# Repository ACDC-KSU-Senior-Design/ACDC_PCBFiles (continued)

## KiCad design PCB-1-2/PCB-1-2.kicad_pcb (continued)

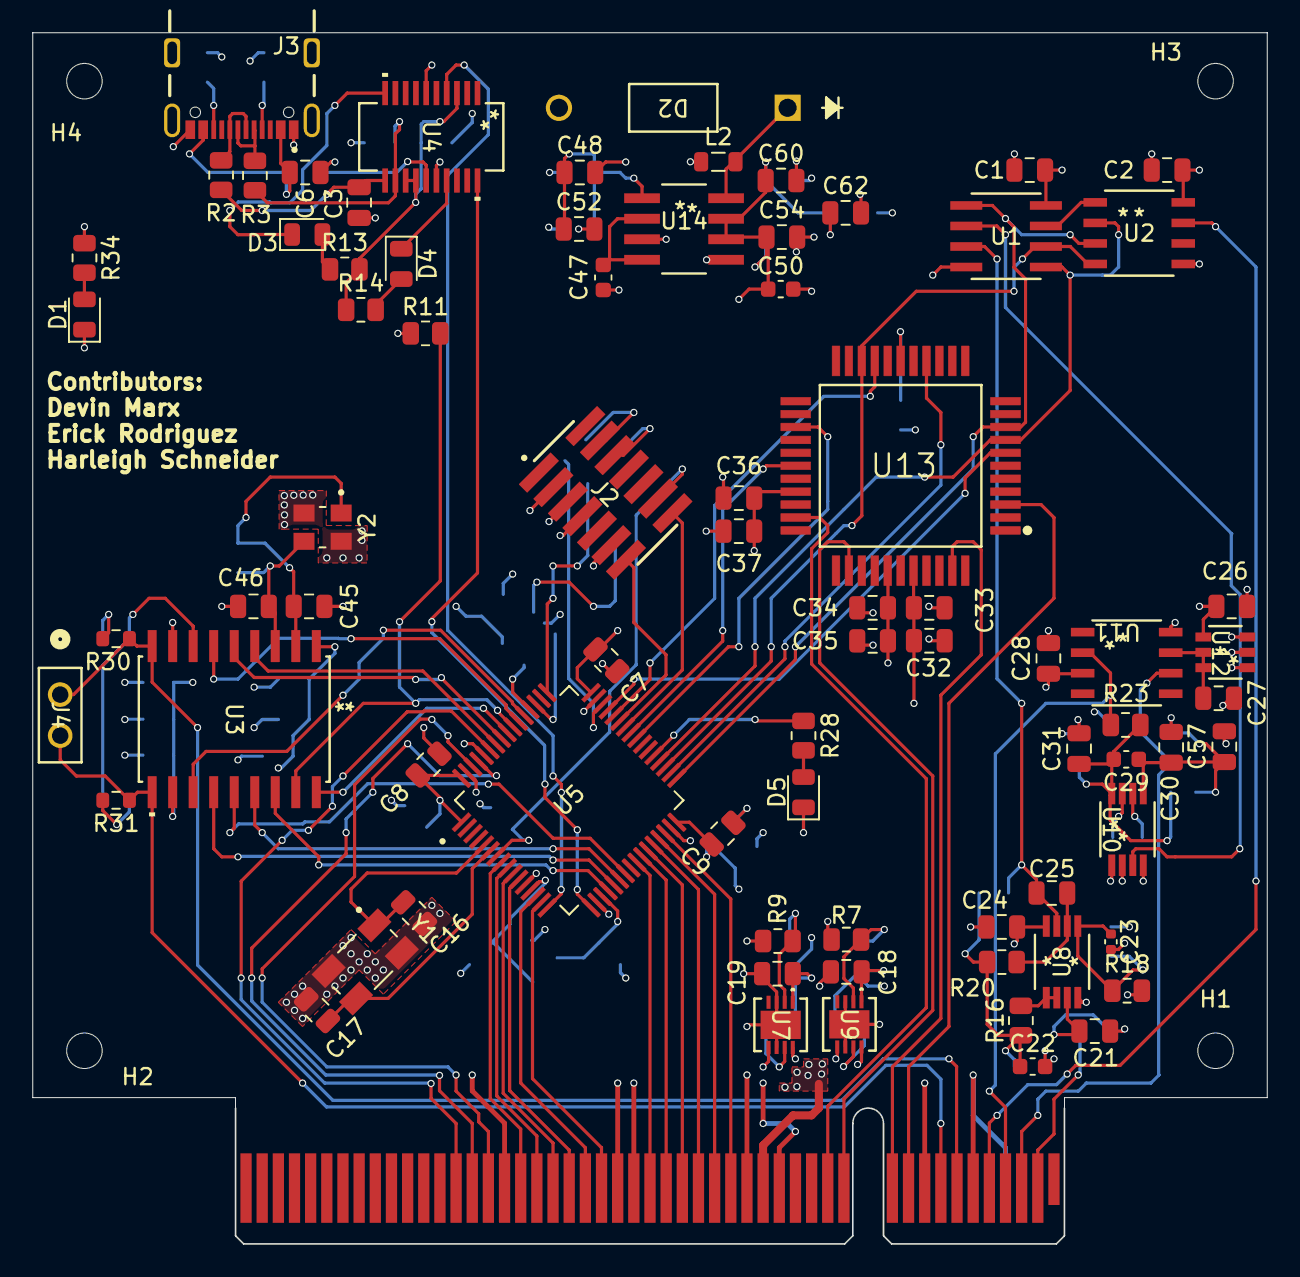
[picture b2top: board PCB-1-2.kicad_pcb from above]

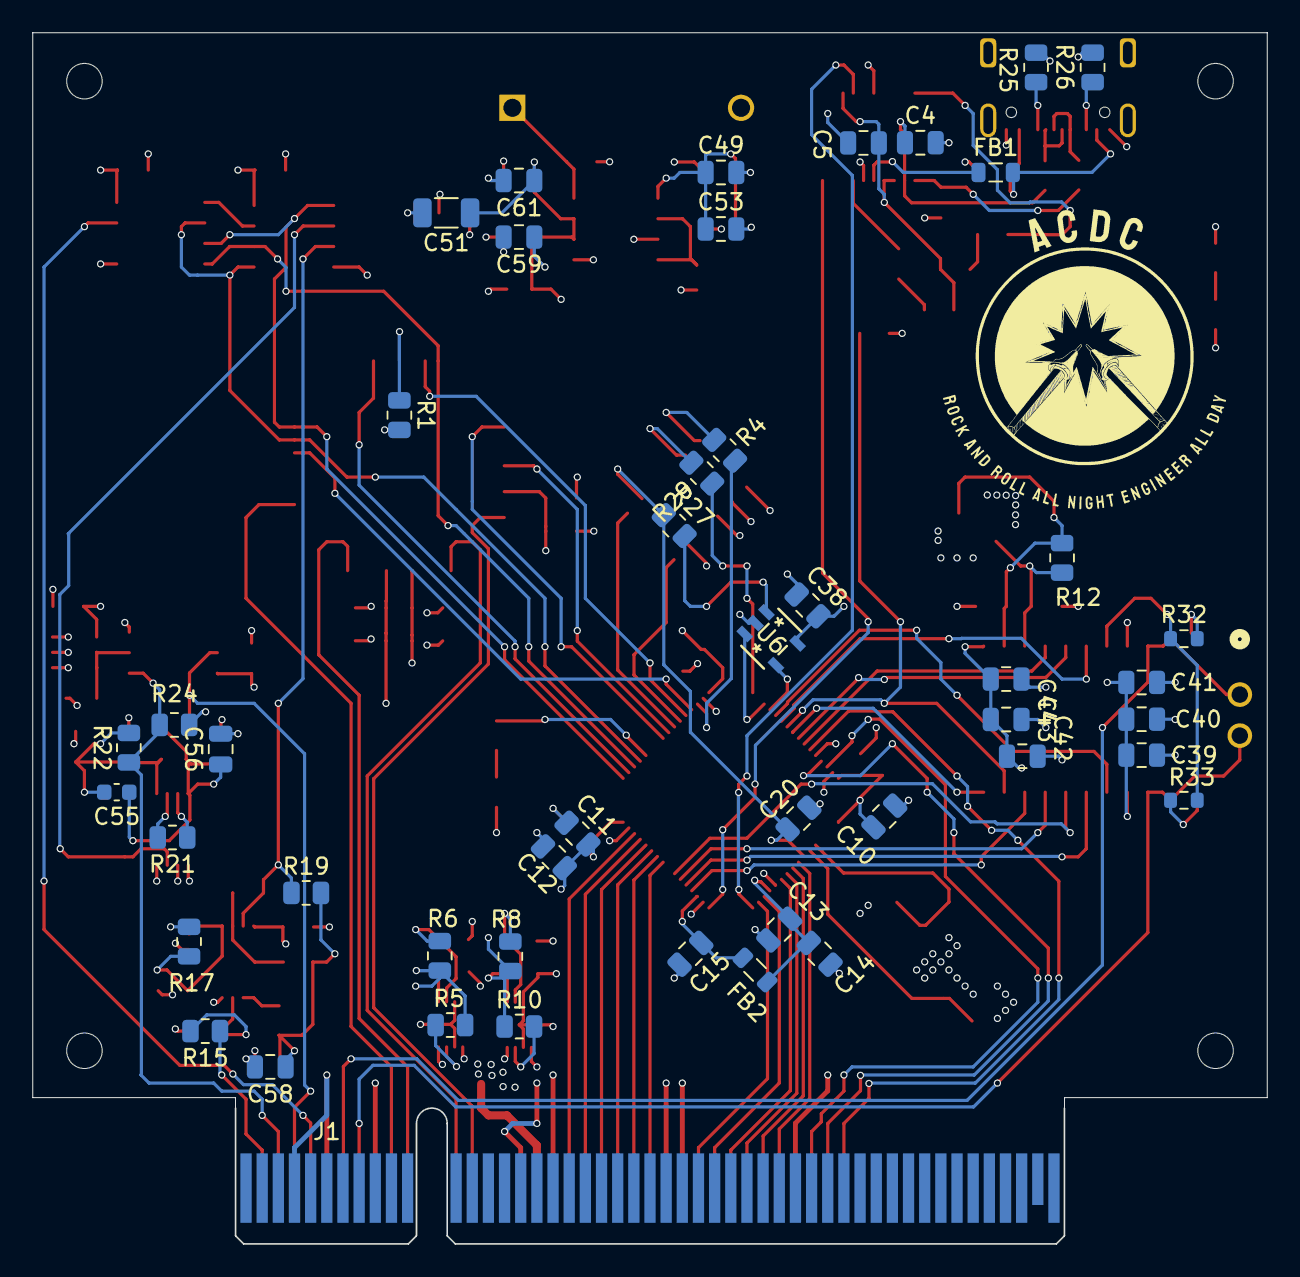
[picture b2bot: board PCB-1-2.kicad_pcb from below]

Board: 4 copper layers, 76.4 x 74.9 mm, 128 parts (47 on the bottom side), 105 nets.

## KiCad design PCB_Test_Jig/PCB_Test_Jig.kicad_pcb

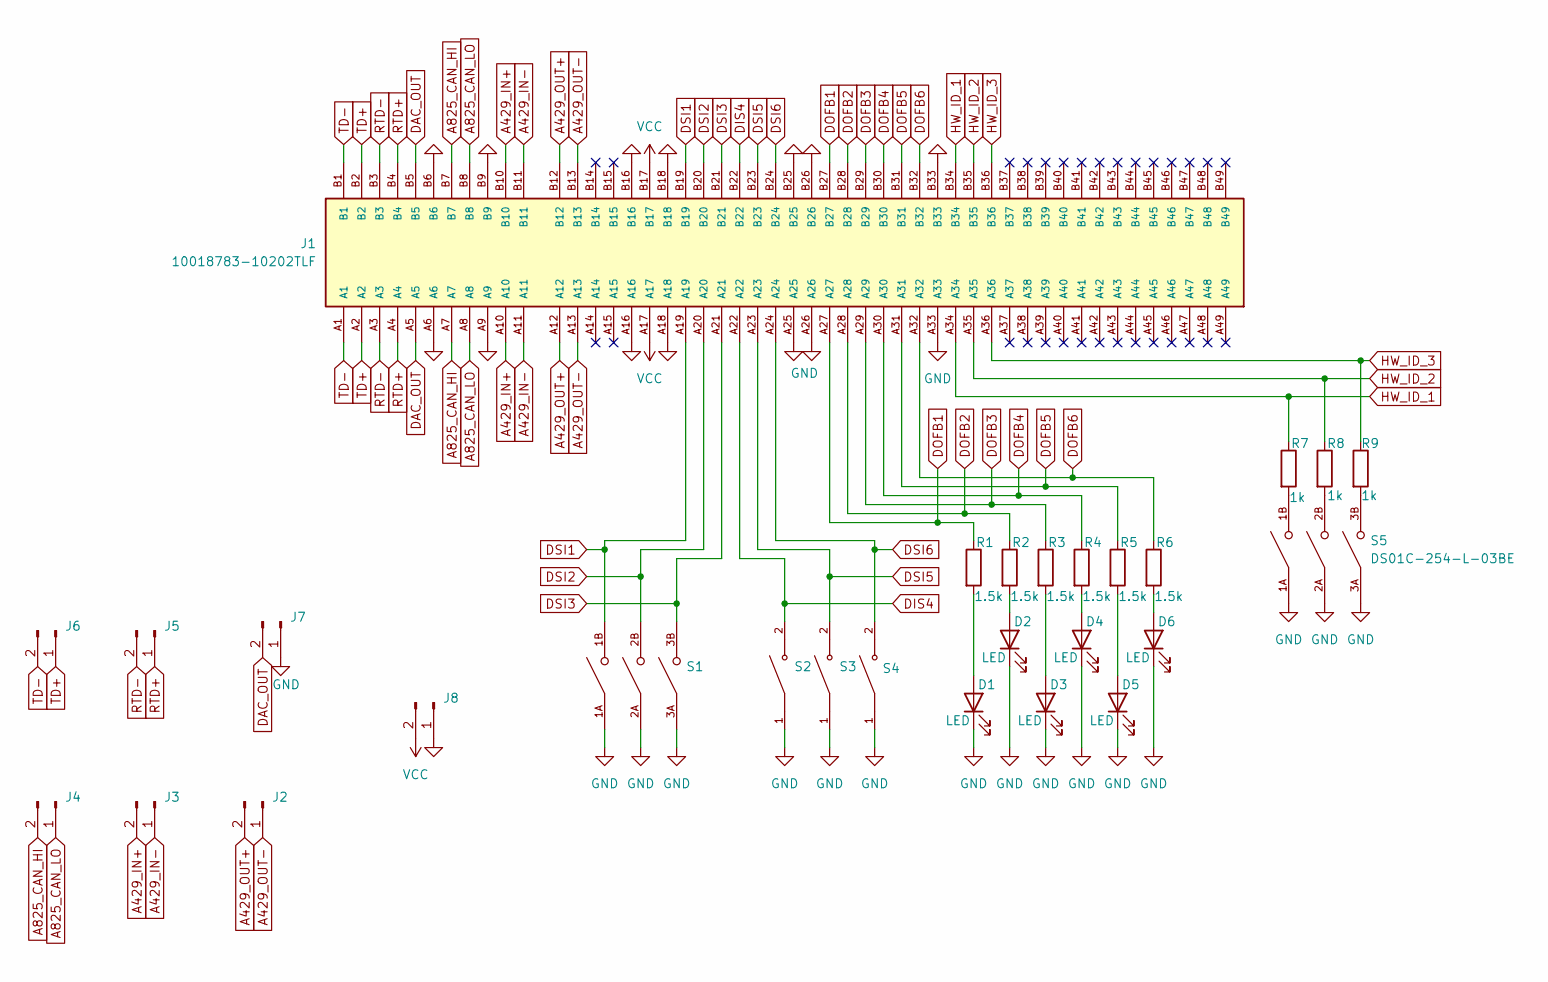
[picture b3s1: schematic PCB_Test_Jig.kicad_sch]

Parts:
D1, D2, D3, D4, D5, D6: LED; LED_0805_2012Metric
J1: 10018783-10202TLF; PCI_Express_Card; PARTREV AA
J2, J3, J4, J5, J6, J7, J8: Conn_01x02_Pin; pin header
R1, R2, R3, R4, R5, R6: 1.5k; R_0805_2012Metric
R7, R8, R9: 1k; R_0805_2012Metric
S1, S5: DS01C-254-L-03BE; SW_DS01C-254-L-03BE; PARTREV 1.0
S2, S3, S4: TS09-63-25-WT-260-SMT-TR; SW_TS09-63-25-WT-260-SMT-TR; PARTREV 1.0

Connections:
A429_IN+: J1.A10, J1.B10, J3.2
A429_IN-: J1.A11, J1.B11, J3.1
A429_OUT+: J1.A12, J1.B12, J2.2
A429_OUT-: J1.A13, J1.B13, J2.1
A825_CAN_HI: J1.A7, J1.B7, J4.2
A825_CAN_LO: J1.A8, J1.B8, J4.1
DAC_OUT: J1.A5, J1.B5, J7.2
DIS4: J1.A22, J1.B22, S2.2
DOFB1: J1.A27, J1.B27, R1.1
DOFB2: J1.A28, J1.B28, R2.1
DOFB3: J1.A29, J1.B29, R3.1
DOFB4: J1.A30, J1.B30, R4.1
DOFB5: J1.A31, J1.B31, R5.1
DOFB6: J1.A32, J1.B32, R6.1
DSI1: J1.A19, J1.B19, S1.1B
DSI2: J1.A20, J1.B20, S1.2B
DSI3: J1.A21, J1.B21, S1.3B
DSI5: J1.A23, J1.B23, S3.2
DSI6: J1.A24, J1.B24, S4.2
GND: D1.1 (K), D2.1 (K), D3.1 (K), D4.1 (K), D5.1 (K), D6.1 (K), J1.A6, J1.A9, J1.A16, J1.A18, J1.A25, J1.A26, J1.A33, J1.B6, J1.B9, J1.B16, J1.B18, J1.B25, J1.B26, J1.B33, J7.1, J8.1, S1.1A, S1.2A, S1.3A, S2.1, S3.1, S4.1, S5.1A, S5.2A, S5.3A
HW_ID_1: J1.A34, J1.B34, R7.1
HW_ID_2: J1.A35, J1.B35, R8.1
HW_ID_3: J1.A36, J1.B36, R9.1
unnamed: D1.2 (A), R1.2
unnamed: D2.2 (A), R2.2
unnamed: D3.2 (A), R3.2
unnamed: D4.2 (A), R4.2
unnamed: D5.2 (A), R5.2
unnamed: D6.2 (A), R6.2
unnamed: R7.2, S5.1B
unnamed: R8.2, S5.2B
unnamed: R9.2, S5.3B
RTD+: J1.A4, J1.B4, J5.1
RTD-: J1.A3, J1.B3, J5.2
TD+: J1.A2, J1.B2, J6.1
TD-: J1.A1, J1.B1, J6.2
VCC: J1.A17, J1.B17, J8.2

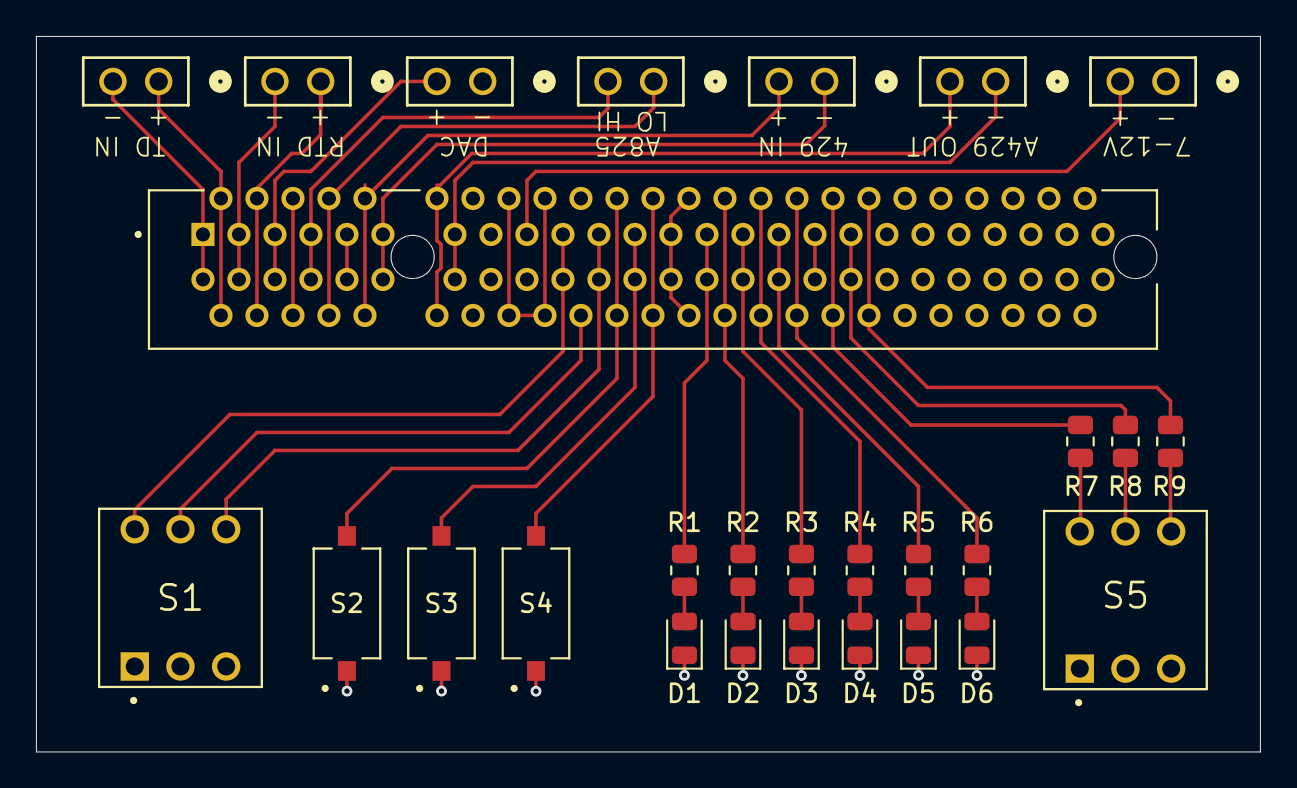
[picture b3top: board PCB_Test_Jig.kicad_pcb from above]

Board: 2 copper layers, 68.0 x 39.8 mm, 28 parts (0 on the bottom side), 37 nets.

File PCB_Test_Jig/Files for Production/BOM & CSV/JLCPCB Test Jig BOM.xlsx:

Comment | Designator | Footprint | JLCPCB Part #（optional）
1k | R9,R7,R8 | R_0805_2012Metric | C17513
1.5k | R1,R4,R5,R2,R3,R6 | R_0805_2012Metric | C4310
LED | D1,D5,D4,D2,D6,D3 | LED_0805_2012Metric | C2297
Conn_01x02_Pin | J8,J3,J6,J4,J7,J2,J5 | pin header
TS09-63-25-WT-260-SMT-TR | S4,S3,S2 | SW_TS09-63-25-WT-260-SMT-TR
DS01C-254-L-03BE | S1,S5 | SW_DS01C-254-L-03BE
10018783-10202TLF | J1 | PCI_Express_Card

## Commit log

2024-03-01 Added ADC, DAC, ARINC 825, & USB 2 UART chip symbols and footprints
2024-03-01 Added Schemaitic for ADC, DAC, USB-C. FT231 is still in progress
2024-03-01 Add files via upload
    Reworked power supply just needs verification from Tim but PCB is getting set up and much simpler schematic!
2024-03-06 Added misc components and added complimentary parts for the MCU
    - Added the ADP7104 5v & 3.3V LDO's
    - Added the Watchdog and connected it
    - Added complimentary components for STM32
    - Figured out the desired crystal and complimentary components
    - Added Debug port for the ST-Link v3-MINIE
    - Assigned footprints for all capacitors and most resistors
2024-03-06 Reformatted the schematic to look cleaner
2024-03-15 Updated a few things
2024-03-21 Finished adding connections to the FTDI chip
2024-03-28 Added more parts and the STEP files (3D models)
2024-03-28 Updated schematic to add the RTD and Transducer signal conditioning
2024-04-03 Added used pins to MCU, also semi wired up 429
    Still need to look a the devboard schematic for the 429 and use its wiring
2024-04-03 Fixed/Updated the USB-C schematic
2024-04-03 Moved a few things around and shrunk the overall schematic size
2024-04-09 Updated Schematic & organized the board layout
2024-04-11 Added -5v Inverter
2024-04-13 Hopefully completed schematic
2024-04-14 Fixing PCIe simple, not done yet
2024-04-16 Merged both -1/-2 and backplane
2024-04-16 Updated -1/-2 and added test jig
2024-04-16 Changed mounting holes and finalized setup
2024-04-16 Addressed Tims comments before ordering
2024-04-16 Updated the test jig
2024-04-16 Adjusted pins connections names
2024-04-16 Added logo
2024-04-16 Changed K to k on resistors
2024-04-16 Generated BOM and POS for backplane
2024-04-17 Generated PCB BOM & CSV
2024-04-17 Generated BOM & CSV for Test Jig
2024-04-17 Updated 3D Model Directory for the backplane
2024-04-17 Located STEP files for -1/-2 and the test jig
2024-04-18 Made final changes (including creating the drill files)
